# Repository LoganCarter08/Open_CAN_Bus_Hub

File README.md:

# Open CAN Bus Hub

An open source alternative to a CAN bus hub primarily used in aftermarket automotive industry.

## Overview

This project is intended to reduce the cost of a simple part needed for many project cars. If you are building a car and need to add aftermarket equipment via CAN bus you will likely need a hub of some sort to distribute the network to each of your devices.

The existing products like [AEM](https://www.aemelectronics.com/products/ev_conversions/wiring_shop/wiring_harnesses/parts/30-2225?srsltid=AfmBOopf-43udBTczr3DMtdVAqn7zBDi4FWJSfJJbkCLwWn_8UP-PhpX), [Haltech](https://www.haltech.com/product/ht-159000-elite-can-hub-4-port-dtm-4/?srsltid=AfmBOop2I1wcCl7ELiAaJ4Hz_9G2S5Ku90I_iyAMGlEmO2NZ8aU0mGMG), and [CANChecked](https://trailbrake.com/canchecked-cbd08-bus-hub/?srsltid=AfmBOopn7O5V_E_J0bepSbhidaalyBVMSegGgtooptUzHmF67YKdkKrH) are very expensive, are limited to a few devices after connecting the ECU, and often require external resistor termination. This project addresses these issues.

This project will walk you through building your own CAN bus hub to meet your needs.

## Design Notes

- The industry standard for automotive CAN bus has become DTM plugs, so utilizing these was a priority
- Minimizing the number of wires to keep complexity and risk of issues was the primary priority. Later versions may attempt to eliminate the need for any wires regardless of number of rows.
- Handling high(ish) current was something we regarded as important as users may be powering many devices from one hub. See the important section for more info on power capabilities.

## IMPORTANT

- Do not exceed 10 amps total on the hub unless you custom order heavier than 2oz copper on the board. This means all of your plugs combined should not exceed 10 amps. It would be ideal to put a fuse prior to the hub to ensure this is not exceeded. Read the PCB readme for more information on amperage.
- Do not exceed 7 amps total on each of the plugs unless you custom order heavier than 2oz copper on the board. The DTM pins are only capable of 7 amps and so is the PCB. Read the PCB readme for more information on amperage.
- This design does not support the DTM waterproof gasket that comes with standard DTM plugs. This is partly due to the high cost of the gasket ($4 each) and partly due to the added complexity for 3D printing. Due to this is it not recommended to use this design in an area that will see direct contact with water or particulates that can cause electrical problems.

## Tools Needed

Note: All Amazon links below are just to serve as an example of what you are looking for. These can be substituted with any equivalent tool.

| **Tool**           | **Details**                                       | **Link**                |
| ------------------ | ------------------------------------------------- | ----------------------- |
| Soldering Iron     | Any will do, but a pointed tip is helpful         | https://amzn.to/42WFt6c |
| 3D Printer         | Read the FAQ if you do not have one.              |                         |
| Allen Keys         | They'll often send some with bolts.               | https://amzn.to/4j0mix5 |
| Needle Nose Pliars | These are not required, but make assembly easier. | https://amzn.to/3GLlzma |
| Wire Strippers     | Only needed if doing more than one row.           | https://amzn.to/4kl7wSS |

## Parts Needed

Note: All Amazon links below are just to serve as an example of what you are looking for. These can be substituted with any equivalent part.

| **Part**            | **Details**                                                               | **Link**                                                                        |
| ------------------- | ------------------------------------------------------------------------- | ------------------------------------------------------------------------------- |
| Solder              | Pretty much any basic solder for electronics should work well.            | https://amzn.to/4mdSlfK                                                         |
| Filament            | I recommend ASA                                                           | https://amzn.to/44zXtVi                                                         |
| DTM Pins            | PN: 0460-202-20141                                                        | https://www.te.com/en/product-0460-202-20141.html                               |
| M2 Bolts            | M2x4mm socket cap                                                         | https://amzn.to/3GLZ6FB                                                         |
| M3 Bolts            | M3x12mm flat cap                                                          | https://amzn.to/3GRSxkQ                                                         |
| M2 Threaded Inserts | M2x3.2mmx4mm                                                              | https://amzn.to/4m9bsb3                                                         |
| M3 Threaded Inserts | M3x5mmx4mm                                                                | https://amzn.to/3EYypgh                                                         |
| 120ohm Resistor     | 1/4 watt                                                                  | https://amzn.to/42SdeFQ                                                         |
| PCBs                | View PCB readme for more info on ordering                                 | https://www.pcbway.com/project/shareproject/Open_CAN_Bus_Hub_V1_0_372ae918.html |
| Wire                | Only needed if doing more than 1 row. Size according to your power needs. |                                                                                 |

## Build/Assemble

1. Follow the [instructions](https://github.com/LoganCarter08/Open_CAN_Bus_Hub/tree/main/Model) in the Model readme for how to make and assemble the case for the hub that houses everything.
2. Follow the [instructions](https://github.com/LoganCarter08/Open_CAN_Bus_Hub/tree/main/PCB) in the PCB readme for how to order and assemble the PCBs.
3. If you are adding a termination resistor, solder it into the PCB that needs it. It is recommended to add it to the last PCB in the hub, furthest from the ECU. Make sure to snip the excess leads flush with the PCB to ensure good fitment into the printed piece and no chances of shorting.
4. Solder the pads between each PCB. This means each pad should be soldered to the corresponding pad on the adjacent PCBs. If you are having a hard time getting your solder to bridge the gap it may be helpful to put a piece of wire without insulation between the boards or even a single strand from a multi strand wire.
   
5. Repeat step 11 for every row in your box.
6. If you have more than 1 row you will need to connect each row with wires here. Make sure to keep the wires as short as possible as any excess will make bolting the bottom half on more difficult. If you need your box to handle higher amperages it is recommended to solder your power and ground wires to the through holes next to the corresponding pads. These will likely provide a better solder point for thicker wires and be more reliable.
7. Using the M3 bolts bolt the bottom half of the hub to the top half.
8. Install into the car and plug in all of your devices!

## FAQ

**Q. How much does it cost to build?**

A. This will depend on how many plugs you need, but a quick breakdown might look like the following. All prices are in USD and estimates based on my purchases. This assumes you have all tools.

| **Part**            | **Cost Estimate Each** | **Quantity**      |
| ------------------- | ---------------------- | ----------------- |
| Pins                | $0.15 - $0.24          | 4 per plug        |
| PCB                 | $0.54 - $5.4           | 1 per plug        |
| Filament            | $0.30 - $0.50          | 1 per plug        |
| M2 Bolts            | $0.08                  | min of 2 per plug |
| M3 Bolts            | $0.17                  | min of 4          |
| M2 Threaded Inserts | $0.06                  | min of 2 per plug |
| M3 Threaded Inserts | $0.09                  | min of 4          |

**Note:** The more PCB you order the cheaper they are. Example: A 10 plug hub should cost around $40 if you only bought 10 PCBs. A 20 plug hub should cost around $50 if you only bought 20 PCBs.

**Q. What pin orientation is used?**

A. The intended orientation is what Link ECU uses, but should also work with Haltech and others. You may notice that in both versions pins 1 and 2 are power and ground and pins 3 and 4 are CAN low and CAN high. Power and ground pins can be interchanged and so can the CAN low and high as long as every device that is plugged into this hub follows this standard. If this isn't clear just think of the markings on the PCB as CAN 1 and CAN 2. They don't actually care if they are high or low. They are just marked to make it easier for assembly. Same with power and ground. These are sized the same internally, so you could use the power pin as the ground and vice versa if you need to for your application.

Link's orientation:

Haltech's orientation (wire side):

**Q. I only need x number of PCBs and it is more expensive to order small amounts.**

A. If you are in the US feel free to contact me. I might have some available and if not I may do a bulk order, depending on interest, to lower the cost per individuals. I can do the same with the pins and resistors too. Shipping outside of the US will likely be more expensive than you ordering them from a manufacturer directly.

**Q. Can I sell these?**

A. I put this project under an MIT license. You are free to sell them if you would like. I just ask that you add a reference back to this project so it can help people who are looking for a DIY solution.

**Q. What if I don't have a 3D printer?**

A. Depending on your budget or needs you can either find a 3D printing service to print it for you, look for local hobbiest with printers, check your local library for printer usage, or you can contact me if you are in the US.

**Q. Do I need to know CAD?**

A. CAD skills are really helpful here. The design is partially parametric, but it is missing brackets for mounting. These will likely need to change per user, so they are not included in the model. I will likely upload some STEP files with some sizes with random mount designs just to give people options. Visit the readme in the Model folder for more information.

**Q. Do I need to know PCB design?**

A. Not unless you need to make changes to the design or want to contribute to the project.

## Disclaimers

- All Amazon links are affiliate links.
- The PCBWay page for the PCB does give me some money for each order placed.

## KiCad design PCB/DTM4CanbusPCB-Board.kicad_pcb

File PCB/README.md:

# Open CAN Bus Hub PCB

The following is intended to help with ordering and assembly of the PCB.

## What Do I Need?

If you plan to modify the PCB or order it from somewhere other than PCBWay you will need KiCad 9.0 or newer.

## Ordering:

If you are in the US and looking to place a small order, feel free to contact me as I might have some that I can ship out. Small batch orders of PCBs are generally much more expensive per board than bulk orders.

### PCBWay:

The design has been shared on PCBWay and can be ordered [here](https://www.pcbway.com/project/shareproject/Open_CAN_Bus_Hub_V1_0_372ae918.html). My suggestion would be to set the edge connector field to "No" versus the default "Yes". If you do not, it is likely PCBWay will contact you to ask you some details about the edge connection. This is not a normal edge connection and can be handled as a solder pad during manufacturing. From there the rest can be default or any other option you may want.

### Other Manufacturers:

1. Open KiCad
2. Press File -> Open Project and select the DTM4CanbusPCB.kicad_pro file from this folder
3. Double click to open the DTM4CanbusPCB-Board.kicad_pcb file
   
4. Press File -> Fabrication Outputs->Gerbers (.gbr)...
   
5. Press Plot in the bottom right
6. Press Generate Drill Files... then press Generate on the next menu
7. Open the newly generated PCB\Gerber folder and zip all of these files up
8. Upload this zip to your favorite PCB manufacturer and place an order.

### Important Notes:

- When ordering it is recommended to use 2oz Cu or heavier for the finished copper. The more plugs in your hub the heavier you will want. Small hubs may be fine with 1oz, but please do research for your use case.

## Assembly Instructions:

1. Bolt each PCB to the top piece of the hub with the M2 bolts. Make sure the resistor is closest to the clip on the plug as shown below. The text on the PCB should be pointed away from the plug.
   
2. Using needle nose pliars insert the DTM pins into the holes on the PCB through the plug.
3. Take a male DTM plug, with the pins in it, and insert it into the female portion of the plug making sure that all of your pins go into the pins on the male plug. You can gently push on the back of your pins to feel for resistance to make sure they are properly aligned and inserted.
4. Solder the pins to the PCB. Make sure you do not heat the pins up too much and melt the housing of your male plug.

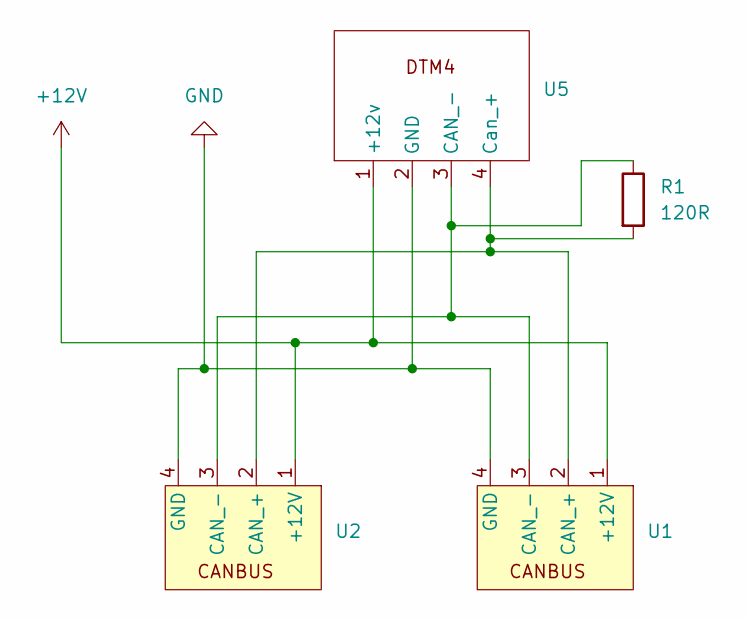
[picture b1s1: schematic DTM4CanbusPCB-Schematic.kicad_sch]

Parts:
R1: 120R; R_Axial_DIN0207_L6.3mm_D2.5mm_P7.62mm_Horizontal
U1: DTM4_CANBUS_Edge_Footprint
U2: DTM4_CANBUS_Edge_Footprint_Mirrored
U5: DTM4_CABUS_Pin_Footprint

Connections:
+12V: U1.1 (+12V), U2.1 (+12V), U5.1 (+12v)
GND: U1.4 (GND), U2.4 (GND), U5.2 (GND)
unnamed: R1.2, U1.2 (CAN_+), U2.2 (CAN_+), U5.4 (Can_+)
unnamed: R1.1, U1.3 (CAN_-), U2.3 (CAN_-), U5.3 (CAN_-)

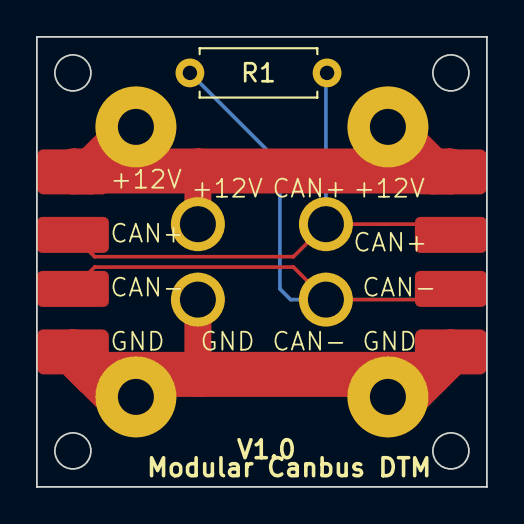
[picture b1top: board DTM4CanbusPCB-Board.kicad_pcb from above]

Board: 2 copper layers, 25.0 x 25.0 mm, 4 parts (0 on the bottom side), 4 nets.

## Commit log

2025-05-05 adding initial pcb design
2025-05-05 adding images that will be used in the readme eventually
2025-05-05 adding initial parametric fusion model
2025-05-05 removing the backup folder that was generated without me realizing
2025-05-06 Create LICENSE
2025-05-06 adding first pass at readme
2025-05-06 adding placeholder readmes
2025-05-06 uploading gitignore in case there are any future contributors
2025-05-06 adding note about gasket not being used
2025-05-06 adding some initial notes about pricing
2025-05-13 adding some links to parts and tools before doing the assembly guide
2025-05-13 fixing some wording and adding clarification on cost section
2025-05-13 adding an additional link as an example of off the shelf solutions
2025-05-14 fixing some issues with the parametric model
2025-05-15 first pass at some of the tutorials
2025-05-15 adding mirrored resistor location to support flipped and rotated PCB mounting
2025-05-15 fixing some typos and doing some rewording
2025-05-15 adding steps about multi row
2025-06-01 adding more information on the readme guides
2025-06-01 small wording changes
